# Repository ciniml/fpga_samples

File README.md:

# FPGA Samples

GOWIN LittleBeeなどの小規模FPGA向けのサンプルやライブラリ

## 内容

### rtl

SystemVerilogで記述したモジュール

### src/main/scala

Chisel3で記述したモジュール

### src/test/scala

Chisel3で記述したモジュールのテスト

## ライセンス

Boost Software License 1.0

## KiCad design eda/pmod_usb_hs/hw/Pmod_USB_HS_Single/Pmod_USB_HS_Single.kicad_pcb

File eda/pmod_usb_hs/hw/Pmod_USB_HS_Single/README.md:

# Pmod USB HS Single (Rev. A)

USB 2.0 HS デバイスを Pmod 1 個でつなぐ基板。Gowin USB 2.0 SoftPHY の Single LVDS 配線から
D- 側の比較器を省き、FPGA ピン 7 本 + VBUS 検出 1 本に収めた。KiCad 10。

- FPGA 側: `rtl/usb/gowin/usb_phy_gowin_sl.v` の `CMP1=1`
- 設計検討: [`../../SINGLE_PMOD.md`](../../SINGLE_PMOD.md)
- PHY の動作確認: SLogic16U3 で HS を実機確認済み (`eda/slogic16u3_usb2`、`make HS=1 CMP1=1`)

状態: **設計のみ (未発注・実機未確認)**。ERC / DRC (回路図との一致を含む) はエラー 0。

## 仕様

- 外形 22.86 × 27.94 mm、2 層 1.6 mm (FR4)、角 1.27 mm 面取り。
- J1: Pmod 2x6 直角ヘッダ (TangFPGAExtensions の `Conn_Pmod_Spec_B_Thin`)、基板下端。
- J2: USB Type-C レセプタクル、HRO TYPE-C-31-M-12 (USB 2.0 の 16 ピン)、基板上端。デバイス (UFP) 専用。
- D+/D- の結合ペア:
  - 寸法は Pmod_RPiCamera と同じ 0.1661 / 0.127 mm (USB ネットクラス)。
  - F.Cu のみで引き、B.Cu は全面 GND。
  - B.Cu を通るのは、コネクタのピン列の D-/D+ 入れ替え 1 か所 (約 2 mm) だけ。ほかに VREF (直流) がヘッダの列の間で B.Cu を通る。
- ESD 保護: D1/D2 は TPD1E05U06DPY (0.42 pF、1 ライン 1 個)。
- VBUS は電源に使わず、検出だけに使う。R12/R13 で 5 V を 3.0 V に分圧する (LVCMOS33 の VIH 2.0 V を超える)。

## 回路 (TN710 USB2.0-RC、Arora-V の値)

| Ref | 値 | 役割 |
|---|---|---|
| R6, R7 | 100 Ω | dx 対の直列抵抗 (TN710 R6/R7)。送信と差動受信がこの対を共用する |
| R2, R3 | 33 Ω | HS 終端 (ピンの Low 駆動 + 33 Ω、TN710 R2/R3 は 36 Ω。JLC の Basic 部品にするため 33 Ω に変更、終端は約 42 Ω の見込み) |
| R1 | 1.5 kΩ | D+ プルアップ。PULLUP が High でアタッチ |
| R8 / R9 | 4.7 kΩ / 200 Ω | VREF = 3.3 V × 200 / 4900 ≈ 135 mV (D+ 比較器の N 側。TN710 は 1.8 kΩ / 75 Ω で 132 mV、Basic 部品にするため変更) |
| C1 | 1 µF | VREF のバイパス |
| R10, R11 | 5.1 kΩ | CC1/CC2 の Rd (UFP) |
| R12 / R13 | 100 kΩ / 150 kΩ | VBUS 検出の分圧 |
| C5 | 1 µF | VBUS |
| C3, C4 | 10 µF, 100 nF | 3.3 V のデカップリング |

- TN710 の R4/R5 (Dual LVDS の差動受信用 0 Ω) は Single 配線にはないので欠番にしてある。
- TN710 の定数表に合わせるため、部品番号はそのまま使っている (R2/R3 と R8/R9 の値は上記のとおり変更)。

## ピン割り当て

| Pmod | 信号 | FPGA の IO | Tang Primer 25K (pmod2) |
|---|---|---|---|
| 1 / 7 | DX_P / DX_N | LVCMOS33D 双方向 (ELVDS_IOBUF) | G11 / G10 |
| 2 / 8 | D+ / VREF | LVDS25 入力 (D+ 比較器) | D11 / D10 |
| 3 / 9 | TERM_DP / TERM_DN | LVCMOS33 双方向 (Low で終端、Hi-Z で FS 受信) | B11 / B10 |
| 4 | PULLUP | LVCMOS33 出力 | C11 |
| 10 | VBUS_DET | LVCMOS33 入力 (PULL_MODE=DOWN) | C10 |
| 5, 11 / 6, 12 | GND / 3.3 V | | |

制約の例と PHY のつなぎ方は `../../SINGLE_PMOD.md` の §3 と §4 にある。

## 配線の要点

- **コネクタのピン列**: 1 列の SMD パッドで D+/D- が交互に並ぶ (B6 D+、A7 D-、A6 D+、B7 D-)。
  - B6 と A6 はピン列の上 (コネクタ本体の下) でつないだ。
  - B7 は B.Cu に潜って D+ の下をくぐり、A7 側の D- に合流する。
  - VBUS の 2 パッドも同様に、ピン列の上でつないだ。
- **ペアからヘッダまで**: ESD のあと、D+/D- はペアのまま斜めに下りてヘッダ直上の TN710 網に入る。
  - D+ はバス状に分岐する: R6、比較器 → Pmod 2 (直進)、R2 → Pmod 3、R1 → Pmod 4。
  - D- は左へ分かれて R7 と R3 に入る。
- **dx 対 (R6/R7 → Pmod 1/7)**: HS の送受信を担うペア。
  - R6/R7 を横に並べ、出口からすぐ結合ペアにしてヘッダの左を下ろす。
  - ヘッダの 2 列の間に横から入り、そこで対称に分かれる (P は上の Pmod 1、N は下の Pmod 7)。
  - Pmod の差動ペアは上下の列で向かい合うので、上から入ると N だけが 2.54 mm 長くなる。横から入ってこれを避けた。
- **D- の終端 (R3 → Pmod 9)**: 基板の左端を下り、ヘッダ外側の列の下を通って Pmod 9 に下から入る。
- **VREF と VBUS_DET**:
  - VREF は Pmod 8 から B.Cu でヘッダの列の間を右へ抜け、ビアで表に戻る。直流で、真上 (F.Cu) に高速の信号はない。
  - VBUS_DET は Pmod 4 と 5 の間からヘッダの列の間 (F.Cu) に入り、Pmod 10 に届く。
- **配線長** (`gen_pcb.py` の基板から計測):
  - DX_P (R6 → Pmod 1) は 6.2 mm、DX_N (R7 → Pmod 7) は 6.7 mm。P/N の差は約 0.5 mm (約 3 ps)。
  - D- の終端経路 (R3 → Pmod 9) は 15.8 mm、D+ 側 (R2 → Pmod 3) は 2.5 mm。

## 製造データ

`tools/build.sh` が ERC / DRC (回路図との一致を含む) を通してから `fab/` を作る。

| ファイル | 内容 |
|---|---|
| `fab/Pmod_USB_HS_Single_gerber.zip` | ガーバー (F/B Cu、Mask、Silk、F.Paste、Edge) とドリル (PTH/NPTH 別) |
| `fab/Pmod_USB_HS_Single_bom.csv` | 部品表 (LCSC 番号、MPN 付き) |
| `fab/Pmod_USB_HS_Single_pos.csv` | 実装位置 (表面のみ) |
| `fab/jlc/Pmod_USB_HS_Single_jlc_bom.csv`, `_jlc_cpl.csv` | JLC 実装用の BOM / CPL (`tools/jlc_files.py`、LCSC 番号のない J1 は除く) |
| `fab/Pmod_USB_HS_Single_schematic.pdf` | 回路図 |
| `fab/*.png` | 3D レンダリング |
| `fab/erc.rpt`, `fab/drc.rpt` | 検査結果 (ライブラリ表の警告はヘッドレス環境に由来) |
| `fab/lcsc/Pmod_USB_HS_Single_lcsc_5pcs.csv` | LCSC 部品購入用 (5 枚分、J1 含む、2026-10-29 時点で約 $5.84)。`tools/lcsc_order.py N` で N 枚分を作り直す (LCSC に問い合わせて最小発注数・単価・在庫を反映、要ネットワーク、`build.sh` には含まない) |

回路図 (`tools/gen_sch.py`) と基板 (`tools/gen_pcb.py`、配置・配線・ベタを座標で記述) は最初スクリプトから生成した。
その後、基板は KiCad で手を入れている (F.Cu の +3V3 ベタ、配線の調整) ので、GUI 側を正とする。
`build.sh` は既定では再生成しない。`REGEN=1 tools/build.sh` で再生成すると GUI での修正は消える。
部品の LCSC 番号と MPN は `tools/gen_sch.py` の `PARTS` が正。変えたら `tools/gen_sch.py` → `tools/update_fields.py`
(配線を残したまま基板側の部品の欄だけ更新) → `tools/build.sh`。
裏面シルク (ロゴ、基板名 / 版 / 日付 / 作者、ピン表) は `tools/silk.py` が持つ。単体で実行すると、基板の裏面シルクだけをその場で入れ直す (銅箔は触らない)。
表面のリファレンス文字は circuitpnr (`cpnr labels`) で置き、`cpnr label-check` で重なり・パッド干渉・取り違えがないことを確かめた
(`gen_pcb.py` は非表示で作るので、`REGEN=1` のあとは置き直しが要る)。

## 部品

LCSC 番号は 2026-10-29 時点。JLC の Basic 部品があるものはそれを選んだ (JLC と LCSC の在庫は別)。JLC の拡張部品 (手数料あり) は D1/D2 と J2 の 2 種類、R13 は Preferred Extended。

| Ref | 部品 | LCSC | 備考 |
|---|---|---|---|
| J1 | 2x6 2.54 mm 直角ピンヘッダ | (C41417354) | 手はんだ。回路図には LCSC 番号なし。購入一覧では左の候補を使う (ピン長・本体寸法をフットプリントと要照合) |
| J2 | HRO TYPE-C-31-M-12 | C165948 | 16 ピン (USB 2.0)。外形 7.3 mm、前端は基板端から約 0.65 mm 出る (要実物確認) |
| D1, D2 | TI TPD1E05U06DPYR | C436349 | X1SON-2 (0.6 × 1.0 mm)。手はんだは難しい。同名の互換品 (TECH PUBLIC C907835、Leiditech C2972479) はクランプ電圧などが違うので使わない |
| R1 | 1.5 kΩ 1% 0402 UNI-ROYAL 0402WGF1501TCE | C25867 | |
| R2, R3 | 33 Ω 1% 0402 UNI-ROYAL 0402WGF330JTCE | C25105 | JLC Basic。LCSC 在庫切れのときは購入一覧で YAGEO RC0402FR-0733RL (C138002) に置き換わる |
| R6, R7 | 100 Ω 1% 0402 UNI-ROYAL 0402WGF1000TCE | C25076 | |
| R8 / R9 | 4.7 kΩ / 200 Ω 1% 0402 UNI-ROYAL | C25900 / C25087 | JLC Basic |
| R10, R11 | 5.1 kΩ 1% 0402 UNI-ROYAL 0402WGF5101TCE | C25905 | |
| R12 / R13 | 100 kΩ / 150 kΩ 1% 0402 UNI-ROYAL | C25741 / C25755 | |
| C1, C5 | 1 µF X5R 0402 Samsung CL05A105KA5NQNC | C52923 | LCSC で在庫切れのときは、購入一覧で YAGEO CC0402KRX5R7BB105 (C325464、16 V) などに置き換わる |
| C3 | 10 µF 10 V X5R 0603 Samsung CL10A106KP8NNNC | C19702 | |
| C4 | 100 nF X7R 0402 Samsung CL05B104KB54PNC | C307331 | LCSC 在庫切れのときは、購入一覧で Samsung CL05B104KO5NNNC (C1525、16 V) に置き換わる |

## 未確定事項

- **差動インピーダンス**: Pmod_RPiCamera と同じ寸法 (100 Ω 想定、2 層 1.6 mm でのペア結合が主体) で、USB の 90 Ω に合わせた計算はしていない。
  - 基板上の D+/D- は約 15 mm で、FPGA ボード側の Pmod 配線とヘッダの方が支配的。
  - 製造業者のスタックアップで要再計算。
- **定数**: R2/R3 と R8/R9 以外は TN710 の Arora-V の値そのままで、HS の振幅 (400 mV) と終端 (33 Ω + IO の ON 抵抗) は未実測。SLogic16U3 の実装値も不明。
  - R6/R7 (直列) と IO の DRIVE で振幅が決まる。
- **Pmod 経由の HS 品質**: 送受信が同じ dx 対を通るので、ヘッダから FPGA までの未整合区間が両方向に効く。`SINGLE_PMOD.md` §7 を参照。
- **Tang Primer 25K の pmod2**: G11/G10 を ELVDS_IOBUF (エミュレート差動の出力) にできるか、960 MHz の FCLK が届くかは合成で未確認。
- **J2**: 基板端に対する前後位置。

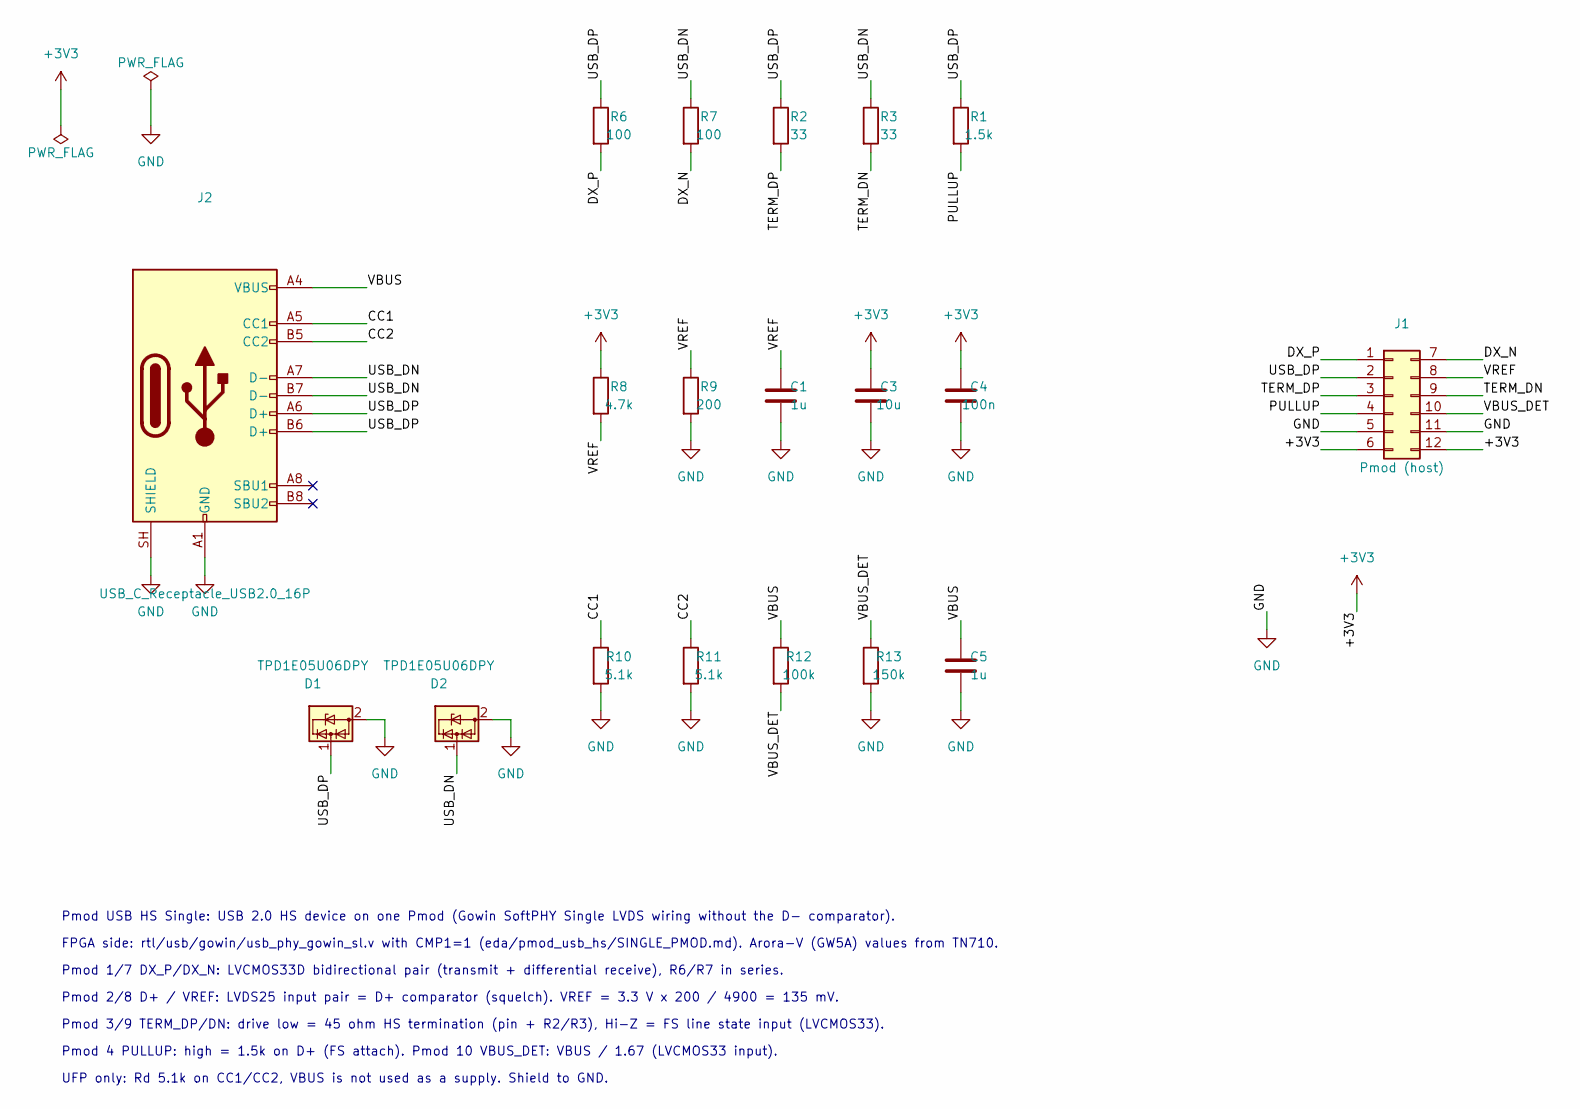
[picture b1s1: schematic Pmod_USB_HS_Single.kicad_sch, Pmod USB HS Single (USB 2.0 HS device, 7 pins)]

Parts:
C1, C5: 1u; C_0402_1005Metric; MPN Samsung CL05A105KA5NQNC; LCSC C52923
C3: 10u; C_0603_1608Metric; MPN Samsung CL10A106KP8NNNC; LCSC C19702
C4: 100n; C_0402_1005Metric; MPN Samsung CL05B104KB54PNC; LCSC C307331
D1, D2: TPD1E05U06DPY; Texas_DPY0002A_0.6x1mm_P0.65mm; MPN TI TPD1E05U06DPYR; LCSC C436349
J1: Pmod (host); Conn_Pmod_Spec_B_Thin
J2: USB_C_Receptacle_USB2.0_16P; USB_C_Receptacle_HRO_TYPE-C-31-M-12; MPN HRO TYPE-C-31-M-12; LCSC C165948
R1: 1.5k; R_0402_1005Metric; MPN UNI-ROYAL 0402WGF1501TCE; LCSC C25867
R2, R3: 33; R_0402_1005Metric; MPN UNI-ROYAL 0402WGF330JTCE; LCSC C25105
R6, R7: 100; R_0402_1005Metric; MPN UNI-ROYAL 0402WGF1000TCE; LCSC C25076
R8: 4.7k; R_0402_1005Metric; MPN UNI-ROYAL 0402WGF4701TCE; LCSC C25900
R9: 200; R_0402_1005Metric; MPN UNI-ROYAL 0402WGF2000TCE; LCSC C25087
R10, R11: 5.1k; R_0402_1005Metric; MPN UNI-ROYAL 0402WGF5101TCE; LCSC C25905
R12: 100k; R_0402_1005Metric; MPN UNI-ROYAL 0402WGF1003TCE; LCSC C25741
R13: 150k; R_0402_1005Metric; MPN UNI-ROYAL 0402WGF1503TCE; LCSC C25755

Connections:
+3V3: C3.1, C4.1, J1.6, J1.12, R8.1
/CC1: J2.A5 (CC1), R10.1
/CC2: J2.B5 (CC2), R11.1
/DX_N: J1.7, R7.2
/DX_P: J1.1, R6.2
/PULLUP: J1.4, R1.2
/TERM_DN: J1.9, R3.2
/TERM_DP: J1.3, R2.2
/USB_DN: D2.1 (I/O), J2.A7 (D-), J2.B7 (D-), R3.1, R7.1
/USB_DP: D1.1 (I/O), J1.2, J2.A6 (D+), J2.B6 (D+), R1.1, R2.1, R6.1
/VBUS: C5.1, J2.A4 (VBUS), J2.A9 (VBUS), J2.B4 (VBUS), J2.B9 (VBUS), R12.1
/VBUS_DET: J1.10, R12.2, R13.1
/VREF: C1.1, J1.8, R8.2, R9.1
GND: C1.2, C3.2, C4.2, C5.2, D1.2 (GND), D2.2 (GND), J1.5, J1.11, J2.A1 (GND), J2.A12 (GND), J2.B1 (GND), J2.B12 (GND), J2.SH (SHIELD), R9.2, R10.2, R11.2, R13.2

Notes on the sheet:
Pmod USB HS Single: USB 2.0 HS device on one Pmod (Gowin SoftPHY Single LVDS wiring without the D- comparator).
FPGA side: rtl/usb/gowin/usb_phy_gowin_sl.v with CMP1=1 (eda/pmod_usb_hs/SINGLE_PMOD.md). Arora-V (GW5A) values from TN710.
Pmod 1/7 DX_P/DX_N: LVCMOS33D bidirectional pair (transmit + differential receive), R6/R7 in series.
Pmod 2/8 D+ / VREF: LVDS25 input pair = D+ comparator (squelch). VREF = 3.3 V x 200 / 4900 = 135 mV.
Pmod 3/9 TERM_DP/DN: drive low = 45 ohm HS termination (pin + R2/R3), Hi-Z = FS line state input (LVCMOS33).
Pmod 4 PULLUP: high = 1.5k on D+ (FS attach). Pmod 10 VBUS_DET: VBUS / 1.67 (LVCMOS33 input).
UFP only: Rd 5.1k on CC1/CC2, VBUS is not used as a supply. Shield to GND.

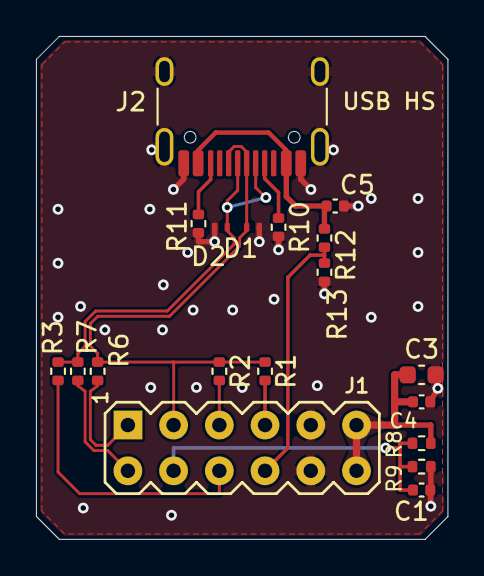
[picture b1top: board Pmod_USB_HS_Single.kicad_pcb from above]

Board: 2 copper layers, 22.9 x 27.9 mm, 20 parts (1 on the bottom side), 14 nets.

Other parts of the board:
LOGO1: Logo_Open_Hardware_Small; logo

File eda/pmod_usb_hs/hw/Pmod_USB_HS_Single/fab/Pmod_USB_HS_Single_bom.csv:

"Reference","Value","Footprint","QUANTITY","LCSC","MPN","Description"
"C1,C5","1u","Capacitor_SMD:C_0402_1005Metric","2","C52923","Samsung CL05A105KA5NQNC","1 uF 10 V X5R 0402 (VBUS),1 uF 10 V X5R 0402 (VREF)"
"C3","10u","Capacitor_SMD:C_0603_1608Metric","1","C19702","Samsung CL10A106KP8NNNC","10 uF 10 V X5R 0603"
"C4","100n","Capacitor_SMD:C_0402_1005Metric","1","C307331","Samsung CL05B104KB54PNC","100 nF 16 V X7R 0402"
"D1,D2","TPD1E05U06DPY","Package_SON:Texas_DPY0002A_0.6x1mm_P0.65mm","2","C436349","TI TPD1E05U06DPYR","1-channel ESD protection, 0.42 pF, X1SON-2"
"J1","Pmod (host)","local:Conn_Pmod_Spec_B_Thin","1","","","Pmod 2x6 right angle (Digilent Pmod Type 1A / spec B)"
"J2","USB_C_Receptacle_USB2.0_16P","Connector_USB:USB_C_Receptacle_HRO_TYPE-C-31-M-12","1","C165948","HRO TYPE-C-31-M-12","USB Type-C receptacle, USB 2.0 (16 pin)"
"R1","1.5k","Resistor_SMD:R_0402_1005Metric","1","C25867","UNI-ROYAL 0402WGF1501TCE","1.5k 1% 0402 (D+ pull-up, soft connect)"
"R2,R3","33","Resistor_SMD:R_0402_1005Metric","2","C25105","UNI-ROYAL 0402WGF330JTCE","33R 1% 0402 (HS termination, D+),33R 1% 0402 (HS termination, D-)"
"R6,R7","100","Resistor_SMD:R_0402_1005Metric","2","C25076","UNI-ROYAL 0402WGF1000TCE","100R 1% 0402 (dx series, D+),100R 1% 0402 (dx series, D-)"
"R8","4.7k","Resistor_SMD:R_0402_1005Metric","1","C25900","UNI-ROYAL 0402WGF4701TCE","4.7k 1% 0402 (VREF ~135 mV)"
"R9","200","Resistor_SMD:R_0402_1005Metric","1","C25087","UNI-ROYAL 0402WGF2000TCE","200R 1% 0402 (VREF)"
"R10,R11","5.1k","Resistor_SMD:R_0402_1005Metric","2","C25905","UNI-ROYAL 0402WGF5101TCE","5.1k 1% 0402 (CC1 Rd),5.1k 1% 0402 (CC2 Rd)"
"R12","100k","Resistor_SMD:R_0402_1005Metric","1","C25741","UNI-ROYAL 0402WGF1003TCE","100k 1% 0402 (VBUS divider, 5 V -> 3.0 V)"
"R13","150k","Resistor_SMD:R_0402_1005Metric","1","C25755","UNI-ROYAL 0402WGF1503TCE","150k 1% 0402 (VBUS divider)"

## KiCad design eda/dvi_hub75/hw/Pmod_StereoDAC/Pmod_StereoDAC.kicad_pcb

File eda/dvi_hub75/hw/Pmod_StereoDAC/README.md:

# Pmod Stereo DAC (Rev. A)

`eda/dvi_hub75` (`rtl/hdmi_rx`) の 1 bit ΔΣ DAC 出力 2 本 (L / R) を、RC ローパスと直流カットを通して
3.5 mm ステレオジャック (と 3 ピンヘッダ) に出す Pmod 基板。ライン出力。KiCad 10。

状態: **設計のみ (未発注・実機未確認)**。ERC / DRC (回路図との一致、ベタ再充填込み) はエラー 0。

## 回路 (チャネルごと、`eda/dvi_hub75/README.md` の LPF そのまま)

```
Pmod 1 (L) / 2 (R) ─ R1 1kΩ ─┬─ R2 10kΩ ─┬─ C3 1µF ─┬─→ ジャック (L = チップ / R = リング) と J3 (1 = L / 3 = R)
                             C1 3.3nF     C2 330pF   R3 100kΩ
                             │            │          │
                            GND          GND        GND
```

| 部品 | L | R | 値 |
|---|---|---|---|
| 1 段目 R / C | R1 / C1 | R11 / C11 | 1 kΩ / 3.3 nF C0G (約 48 kHz) |
| 2 段目 R / C | R2 / C2 | R12 / C12 | 10 kΩ / 330 pF C0G (約 48 kHz) |
| 直流カット | C3 | C13 | 1 µF X7R 50 V (0805) |
| ブリーダ | R3 | R13 | 100 kΩ (出力側の直流を 0 V に固定、抜き差しのポップ防止) |

- 周波数特性 (ピンの出力インピーダンス 30 Ω 込み、dvi_hub75 の計算): −3 dB 28.5 kHz、20 kHz で −1.6 dB、
  1 MHz で −53 dB、ΔΣ の更新周波数 6.19 MHz で −85 dB
- 20 kHz まで平坦にしたいなら C1 / C11 = 2.2 nF、C2 / C12 = 220 pF (−3 dB 約 43 kHz、20 kHz で −0.7 dB、
  6.19 MHz で約 −77 dB)。基板はそのまま、部品の値だけ変える
- 低域: C3 と R3 / 負荷 (47 kΩ 以上を想定) で −3 dB は 2〜4 Hz
- **ライン出力** (フルスケール正弦波で約 1.1 Vrms、出力インピーダンス約 10 kΩ)。**ヘッドホンは直接鳴らせない**
  (アンプ付きスピーカー、オーディオインターフェースのライン入力、ヘッドホンアンプにつなぐ)
- 音質は FPGA の I/O 電源のノイズで決まる (ΔΣ の出力は I/O 電源の電圧そのもの)。改善策は dvi_hub75 の README
  (静かな電源のフリップフロップで打ち直す) を参照。本基板は受動部品のみで 3.3 V は使わない

## コネクタ

| Pmod | 信号 | 備考 |
|---|---|---|
| 1 | AUDIO_L (ΔΣ 左) | |
| 2 | AUDIO_R (ΔΣ 右) | |
| 5, 11 | GND | |
| 3, 4, 7–10, 6 / 12 (3.3 V) | 未接続 | |

- J2: 3.5 mm ステレオジャック SHOU HAN **PJ-313D** (SMD、LCSC C668608)。チップ = L、リング = R、スリーブ = GND。
  プラグ挿入口は基板上端 (本体前面が基板端、ノーズ 2.5 mm がはみ出す)。各接点は 2 本足 (両側) で、
  フットプリントでは同じ番号のパッドを内部接続扱い (duplicate pad numbers are jumpers) にしてある
- J3: 1×3 2.54 mm ピンヘッダ (縦、LCSC C49257)、**1 = L、2 = GND、3 = R** (シルク L / G / R、ピン 1 は角パッド)。
  ジャックと並列 (直流カットの後、ブリーダ付き)。GND が中央なので、逆向きに挿しても L と R が短絡しない
- J1: Pmod 2×6 直角ヘッダ (TangFPGAExtensions の `Conn_Pmod_Spec_B_Thin`)、基板下端、ピン 1 左

FPGA 側の定義は `mod/pmod_stereo_dac/pmod_pins.csv` (dac_l = pmodN_1、dac_r = pmodN_2)。

### eda/dvi_hub75 で使う場合

dvi_hub75 は ΔΣ を J4 (40 ピンヘッダ) の 19 / 20 番 = D1 / E3 から出している。Tang Primer 25K の Pmod 3 スロットは
すべて使用中 (pmod0 = Pmod DVI、pmod1 / pmod2 = HUB75 ベースボード) なので、この基板は **J4 から Pmod を
取り出すアダプタ** (`eda/targets/tangprimer25k/hw` で別途設計中の J4 → Pmod 変換基板) に挿す。
`eda/dvi_hub75/src/tangprimer25k/pins.cst` の `dac_l` / `dac_r` の IO_LOC を、そのアダプタで本基板の
ピン 1 / 2 が来る FPGA ピンに変える (dvi_hub75 の設計自体はまだ変えていない)。
J4 19 / 20 番がアダプタの Pmod ピン 1 / 2 に来る配置なら pins.cst の変更は不要。

## 基板

- 外形 20.32 × 33.6 mm (Pmod 1 スロット幅)、2 層 1.6 mm、角 1.27 mm 面取り
- 2 チャネルを左右の列に配置 (L は Pmod ピン 1 の真上、R は鏡像)。直列部品は列上、信号は下から上 (ジャック側) へ。
  シャント部品 (C1 / C2 / R3) は列の内側に置き、それぞれ専用の GND ビアで裏面の全面 GND へ落とす
- 部品は 0603 (C3 / C13 のみ 0805)、手はんだも可
- 裏面: ロゴ、「Pmod / Stereo DAC / Rev.A / 2026-10-20」「Kenta Ida (@ciniml)」、Pmod ピンの凡例

## 部品 (LCSC / JLCPCB、2026-10-20 時点)

| Ref | 部品 | LCSC | 備考 |
|---|---|---|---|
| R1, R11 | UNI-ROYAL 0603WAF1001T5E (1 kΩ) | C21190 | JLC Basic。LCSC 在庫 0 → 購入リストは YAGEO RC0603FR-071KL (C22548) |
| R2, R12 | UNI-ROYAL 0603WAF1002T5E (10 kΩ) | C25804 | JLC Basic |
| R3, R13 | UNI-ROYAL 0603WAF1003T5E (100 kΩ) | C25803 | JLC Basic |
| C1, C11 | YAGEO CC0603JRNPO9BN332 (3.3 nF C0G) | C107048 | |
| C2, C12 | Samsung CL10C331JB8NNNC (330 pF C0G) | C1664 | JLC Basic |
| C3, C13 | Samsung CL21B105KBFNNNE (1 µF X7R 50 V 0805) | C28323 | JLC Basic。LCSC 在庫 0 → 購入リストは YAGEO CC0805KKX7R9BB105 (C91185) |
| J2 | SHOU HAN PJ-313D | C668608 | |
| J3 | BOOMELE 2.54-1*3P | C49257 | 手はんだ可 |
| J1 | 2×6 2.54 mm 直角ピンヘッダ | — | 手はんだ想定 (購入リストには候補 C41417354、寸法はフットプリントと要照合) |

## 製造データ (`tools/build.sh`)

| ファイル | 内容 |
|---|---|
| `fab/Pmod_StereoDAC_gerber.zip` | ガーバー + ドリル (PTH / NPTH 別) |
| `fab/Pmod_StereoDAC_bom.csv`, `_pos.csv` | 部品表 (LCSC / MPN 付き)、実装位置 (原点は基板左下) |
| `fab/jlc/` | JLCPCB 実装用 BOM / CPL (LCSC 番号のある部品。J3 は THT) |
| `fab/lcsc/Pmod_StereoDAC_lcsc_5pcs.csv` | LCSC 購入リスト 5 枚分 (`tools/lcsc_order.py N`、LCSC 在庫切れは同等品に自動置換) |
| `fab/Pmod_StereoDAC_schematic.pdf`, `*.png` | 回路図、レンダリング |

回路図・基板は `tools/gen_sch.py` / `tools/gen_pcb.py` で生成 (`./tools/build.sh --regen`)。KiCad で手を入れたら
以後は KiCad のファイルが正 (`--regen` は手修正を消す)。

## 未確認・注意

- PJ-313D のフットプリントは SHOU HAN の図面 (2020-08-24) から自作。KiCad 標準ライブラリに該当品が無いため。
  3D モデルは無い (レンダリングにジャックは写らない)。A / B / C 端子 = スリーブ / リング / チップは、
  挿入口に近い順 (A) とデータシートの接続図 (A が本体側) からの判断
- 実機のアナログ特性 (ノイズ、歪み) は未測定 (dvi_hub75 でも LPF 出力は未確認)

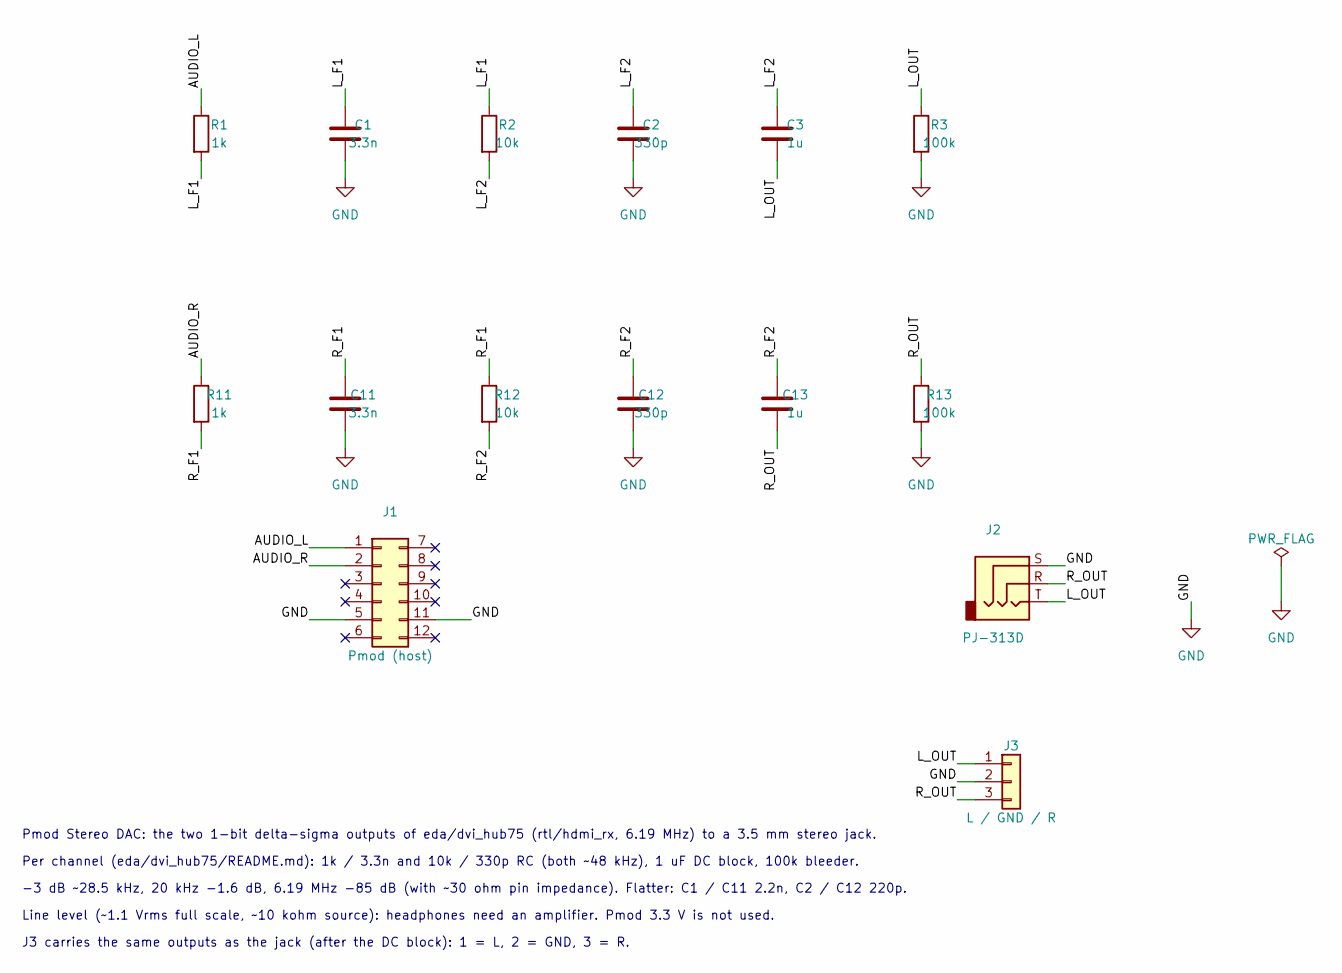
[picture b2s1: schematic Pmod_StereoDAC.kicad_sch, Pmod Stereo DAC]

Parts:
C1, C11: 3.3n; C_0603_1608Metric; MPN YAGEO CC0603JRNPO9BN332; LCSC C107048
C2, C12: 330p; C_0603_1608Metric; MPN Samsung CL10C331JB8NNNC; LCSC C1664
C3, C13: 1u; C_0805_2012Metric; MPN Samsung CL21B105KBFNNNE; LCSC C28323
J1: Pmod (host); Conn_Pmod_Spec_B_Thin; MPN 2x6 2.54 mm right-angle pin header (han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
J2: PJ-313D; Jack_3.5mm_SHOUHAN_PJ-313D_Horizontal; MPN SHOU HAN PJ-313D; LCSC C668608
J3: L / GND / R; PinHeader_1x03_P2.54mm_Vertical; MPN BOOMELE 2.54-1*3P; LCSC C49257
R1, R11: 1k; R_0603_1608Metric; MPN UNI-ROYAL 0603WAF1001T5E; LCSC C21190
R2, R12: 10k; R_0603_1608Metric; MPN UNI-ROYAL 0603WAF1002T5E; LCSC C25804
R3, R13: 100k; R_0603_1608Metric; MPN UNI-ROYAL 0603WAF1003T5E; LCSC C25803

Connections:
/AUDIO_L: J1.1, R1.1
/AUDIO_R: J1.2, R11.1
/L_F1: C1.1, R1.2, R2.1
/L_F2: C2.1, C3.1, R2.2
/L_OUT: C3.2, J2.T, J3.1, R3.1
/R_F1: C11.1, R11.2, R12.1
/R_F2: C12.1, C13.1, R12.2
/R_OUT: C13.2, J2.R, J3.3, R13.1
GND: C1.2, C2.2, C11.2, C12.2, J1.5, J1.11, J2.S, J3.2, R3.2, R13.2

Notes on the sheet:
Pmod Stereo DAC: the two 1-bit delta-sigma outputs of eda/dvi_hub75 (rtl/hdmi_rx, 6.19 MHz) to a 3.5 mm stereo jack.
Per channel (eda/dvi_hub75/README.md): 1k / 3.3n and 10k / 330p RC (both ~48 kHz), 1 uF DC block, 100k bleeder.
-3 dB ~28.5 kHz, 20 kHz -1.6 dB, 6.19 MHz -85 dB (with ~30 ohm pin impedance). Flatter: C1 / C11 2.2n, C2 / C12 220p.
Line level (~1.1 Vrms full scale, ~10 kohm source): headphones need an amplifier. Pmod 3.3 V is not used.
J3 carries the same outputs as the jack (after the DC block): 1 = L, 2 = GND, 3 = R.

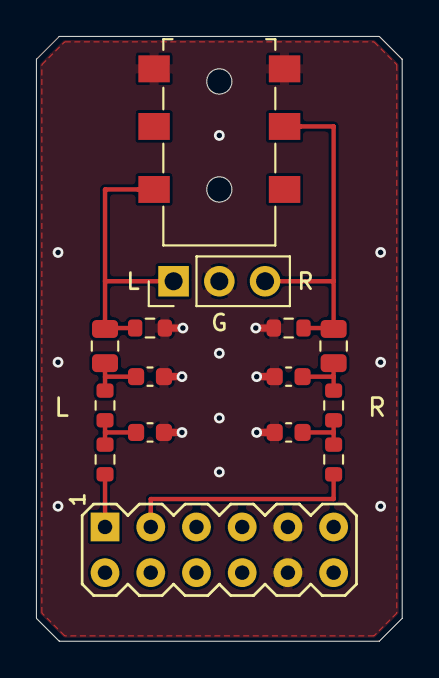
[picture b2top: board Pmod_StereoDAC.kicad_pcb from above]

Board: 2 copper layers, 20.3 x 33.6 mm, 16 parts (1 on the bottom side), 9 nets.

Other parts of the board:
LOGO1: logo

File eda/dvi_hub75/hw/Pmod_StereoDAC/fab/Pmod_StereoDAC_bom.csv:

"Reference","Value","Footprint","QUANTITY","LCSC","MPN","Description"
"C1,C11","3.3n","Capacitor_SMD:C_0603_1608Metric","2","C107048","YAGEO CC0603JRNPO9BN332","3.3 nF 50 V C0G 5% 0603"
"C2,C12","330p","Capacitor_SMD:C_0603_1608Metric","2","C1664","Samsung CL10C331JB8NNNC","330 pF 50 V C0G 5% 0603"
"C3,C13","1u","Capacitor_SMD:C_0805_2012Metric","2","C28323","Samsung CL21B105KBFNNNE","1 uF 50 V X7R 10% 0805 (DC block)"
"J1","Pmod (host)","local:Conn_Pmod_Spec_B_Thin","1","","2x6 2.54 mm right-angle pin header (hand soldered)","Pmod 2x6 right angle (Digilent Pmod Type 1A / spec B)"
"J2","PJ-313D","local:Jack_3.5mm_SHOUHAN_PJ-313D_Horizontal","1","C668608","SHOU HAN PJ-313D","3.5 mm stereo jack, SMD (SHOU HAN PJ-313D): tip = L, ring = R, sleeve = GND"
"J3","L / GND / R","Connector_PinHeader_2.54mm:PinHeader_1x03_P2.54mm_Vertical","1","C49257","BOOMELE 2.54-1*3P","1x03 2.54 mm pin header, vertical: 1 = L, 2 = GND, 3 = R (line out, after the DC block)"
"R1,R11","1k","Resistor_SMD:R_0603_1608Metric","2","C21190","UNI-ROYAL 0603WAF1001T5E","1 kOhm 1% 0603"
"R2,R12","10k","Resistor_SMD:R_0603_1608Metric","2","C25804","UNI-ROYAL 0603WAF1002T5E","10 kOhm 1% 0603"
"R3,R13","100k","Resistor_SMD:R_0603_1608Metric","2","C25803","UNI-ROYAL 0603WAF1003T5E","100 kOhm 1% 0603"

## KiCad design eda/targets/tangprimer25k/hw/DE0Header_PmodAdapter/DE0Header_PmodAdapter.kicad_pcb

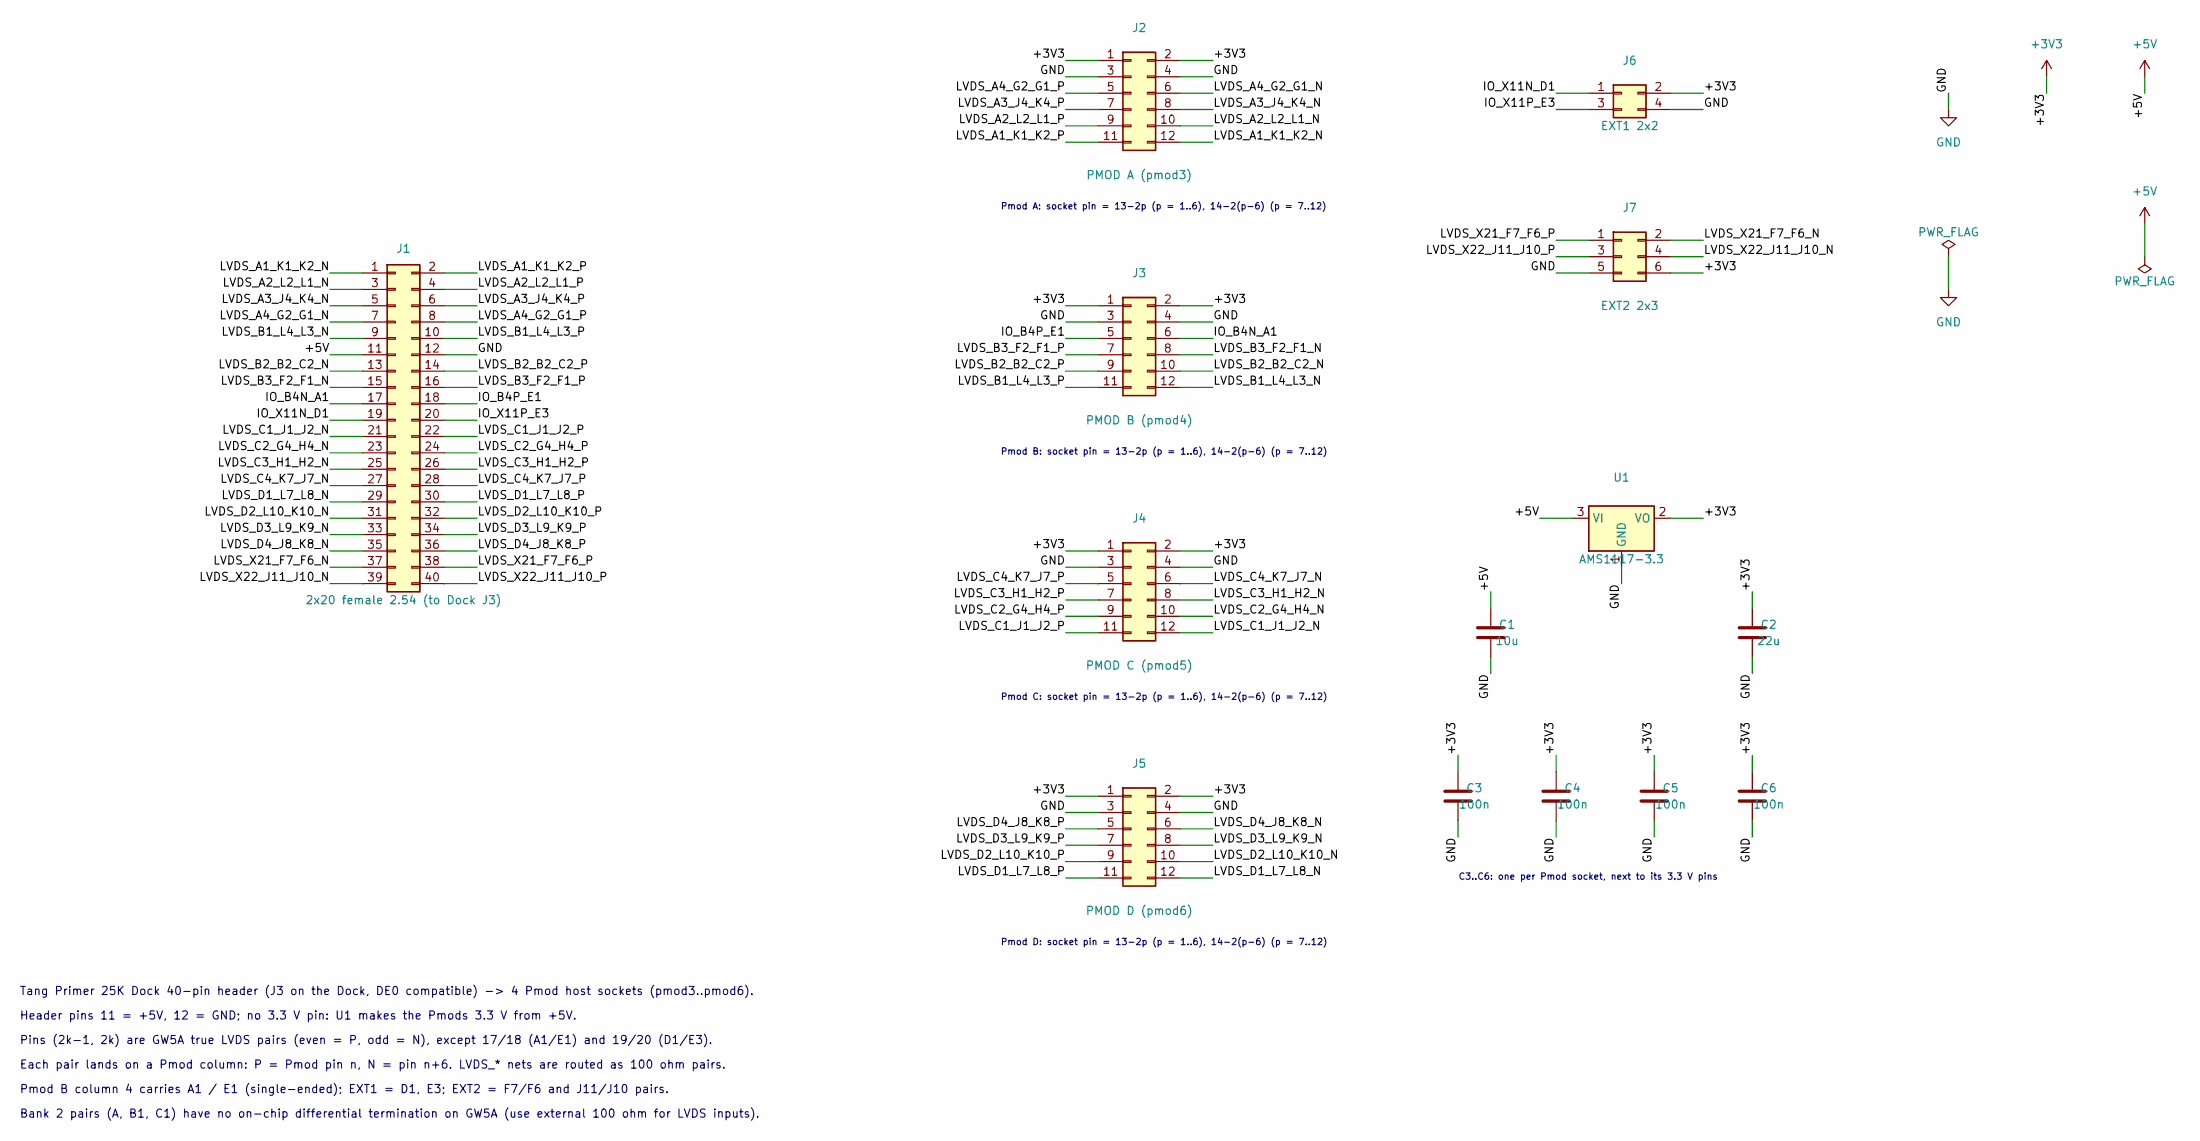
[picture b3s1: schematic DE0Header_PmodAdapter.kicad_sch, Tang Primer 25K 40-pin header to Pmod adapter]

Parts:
C1: 10u; C_0805_2012Metric; MPN Samsung CL21A106KAYNNNE; LCSC C15850
C2: 22u; C_0805_2012Metric; MPN Samsung CL21A226MAQNNNE; LCSC C45783
C3, C4, C5, C6: 100n; C_0402_1005Metric; MPN Samsung CL05B104KO5NNNC; LCSC C1525
J1: 2x20 female 2.54 (to Dock J3); PinSocket_2x20_P2.54mm_Vertical; MPN BOOMELE 2.54-2*20P; LCSC C5124634
J2: PMOD A (pmod3); PinSocket_2x06_P2.54mm_Horizontal; MPN Hong Cheng HC-PM254-8.5H-2x6PW; LCSC C22373932
J3: PMOD B (pmod4); PinSocket_2x06_P2.54mm_Horizontal; MPN Hong Cheng HC-PM254-8.5H-2x6PW; LCSC C22373932
J4: PMOD C (pmod5); PinSocket_2x06_P2.54mm_Horizontal; MPN Hong Cheng HC-PM254-8.5H-2x6PW; LCSC C22373932
J5: PMOD D (pmod6); PinSocket_2x06_P2.54mm_Horizontal; MPN Hong Cheng HC-PM254-8.5H-2x6PW; LCSC C22373932
J6: EXT1 2x2; PinHeader_2x02_P2.54mm_Vertical; MPN BOOMELE 2.54-2*2PPin; LCSC C66690
J7: EXT2 2x3; PinHeader_2x03_P2.54mm_Vertical; MPN BOOMELE 2.54-2*3PPin; LCSC C65114
U1: AMS1117-3.3; SOT-223-3_TabPin2; MPN AMS AMS1117-3.3; LCSC C6186

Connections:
+3V3: C2.1, C3.1, C4.1, C5.1, C6.1, J2.1, J2.2, J3.1, J3.2, J4.1, J4.2, J5.1, J5.2, J6.2, J7.6, U1.2 (VO)
+5V: C1.1, J1.11, U1.3 (VI)
/IO_B4N_A1: J1.17, J3.6
/IO_B4P_E1: J1.18, J3.5
/IO_X11N_D1: J1.19, J6.1
/IO_X11P_E3: J1.20, J6.3
/LVDS_A1_K1_K2_N: J1.1, J2.12
/LVDS_A1_K1_K2_P: J1.2, J2.11
/LVDS_A2_L2_L1_N: J1.3, J2.10
/LVDS_A2_L2_L1_P: J1.4, J2.9
/LVDS_A3_J4_K4_N: J1.5, J2.8
/LVDS_A3_J4_K4_P: J1.6, J2.7
/LVDS_A4_G2_G1_N: J1.7, J2.6
/LVDS_A4_G2_G1_P: J1.8, J2.5
/LVDS_B1_L4_L3_N: J1.9, J3.12
/LVDS_B1_L4_L3_P: J1.10, J3.11
/LVDS_B2_B2_C2_N: J1.13, J3.10
/LVDS_B2_B2_C2_P: J1.14, J3.9
/LVDS_B3_F2_F1_N: J1.15, J3.8
/LVDS_B3_F2_F1_P: J1.16, J3.7
/LVDS_C1_J1_J2_N: J1.21, J4.12
/LVDS_C1_J1_J2_P: J1.22, J4.11
/LVDS_C2_G4_H4_N: J1.23, J4.10
/LVDS_C2_G4_H4_P: J1.24, J4.9
/LVDS_C3_H1_H2_N: J1.25, J4.8
/LVDS_C3_H1_H2_P: J1.26, J4.7
/LVDS_C4_K7_J7_N: J1.27, J4.6
/LVDS_C4_K7_J7_P: J1.28, J4.5
/LVDS_D1_L7_L8_N: J1.29, J5.12
/LVDS_D1_L7_L8_P: J1.30, J5.11
/LVDS_D2_L10_K10_N: J1.31, J5.10
/LVDS_D2_L10_K10_P: J1.32, J5.9
/LVDS_D3_L9_K9_N: J1.33, J5.8
/LVDS_D3_L9_K9_P: J1.34, J5.7
/LVDS_D4_J8_K8_N: J1.35, J5.6
/LVDS_D4_J8_K8_P: J1.36, J5.5
/LVDS_X21_F7_F6_N: J1.37, J7.2
/LVDS_X21_F7_F6_P: J1.38, J7.1
/LVDS_X22_J11_J10_N: J1.39, J7.4
/LVDS_X22_J11_J10_P: J1.40, J7.3
GND: C1.2, C2.2, C3.2, C4.2, C5.2, C6.2, J1.12, J2.3, J2.4, J3.3, J3.4, J4.3, J4.4, J5.3, J5.4, J6.4, J7.5, U1.1 (GND)

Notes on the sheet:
Pmod A: socket pin = 13-2p (p = 1..6), 14-2(p-6) (p = 7..12)
Pmod B: socket pin = 13-2p (p = 1..6), 14-2(p-6) (p = 7..12)
Pmod C: socket pin = 13-2p (p = 1..6), 14-2(p-6) (p = 7..12)
Pmod D: socket pin = 13-2p (p = 1..6), 14-2(p-6) (p = 7..12)
C3..C6: one per Pmod socket, next to its 3.3 V pins
Tang Primer 25K Dock 40-pin header (J3 on the Dock, DE0 compatible) -> 4 Pmod host sockets (pmod3..pmod6).
Header pins 11 = +5V, 12 = GND; no 3.3 V pin: U1 makes the Pmods 3.3 V from +5V.
Pins (2k-1, 2k) are GW5A true LVDS pairs (even = P, odd = N), except 17/18 (A1/E1) and 19/20 (D1/E3).
Each pair lands on a Pmod column: P = Pmod pin n, N = pin n+6. LVDS_* nets are routed as 100 ohm pairs.
Pmod B column 4 carries A1 / E1 (single-ended); EXT1 = D1, E3; EXT2 = F7/F6 and J11/J10 pairs.
Bank 2 pairs (A, B1, C1) have no on-chip differential termination on GW5A (use external 100 ohm for LVDS inputs).

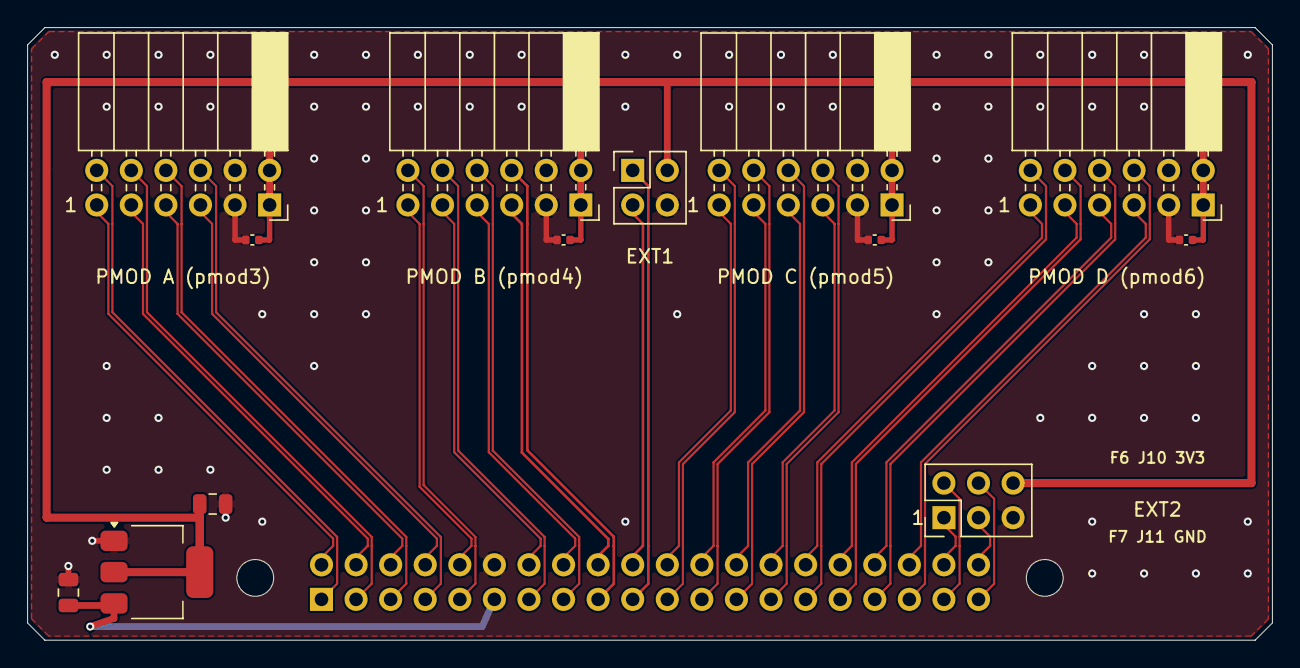
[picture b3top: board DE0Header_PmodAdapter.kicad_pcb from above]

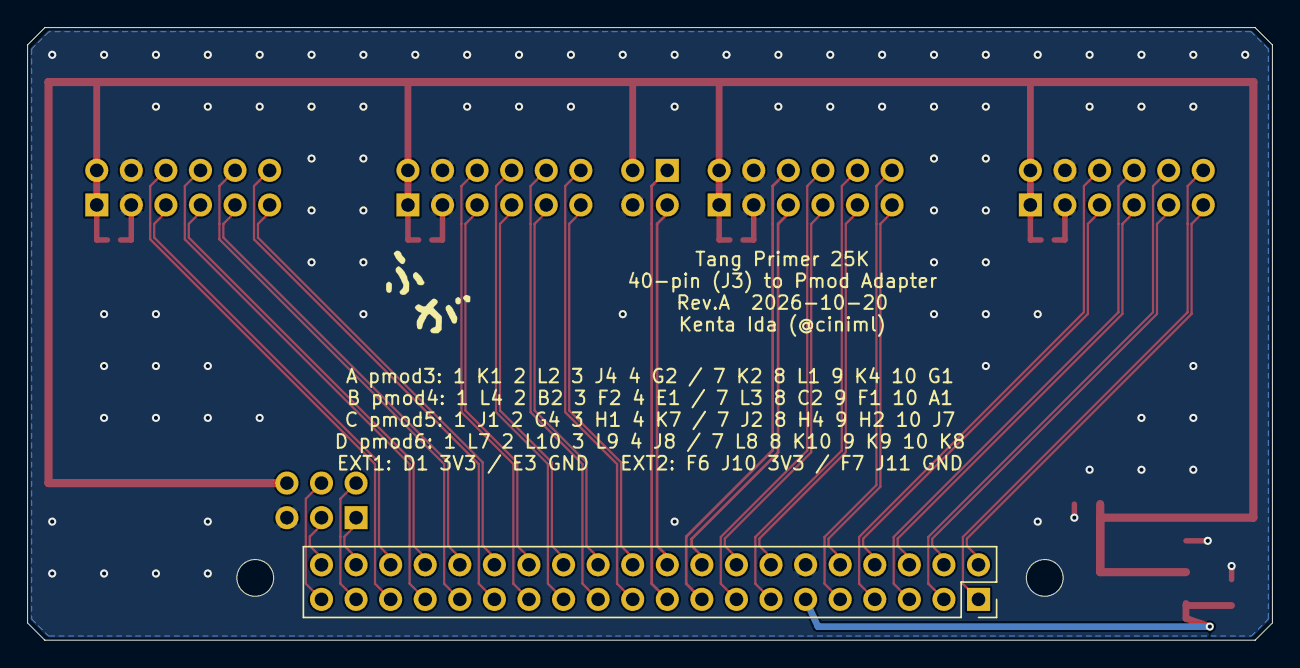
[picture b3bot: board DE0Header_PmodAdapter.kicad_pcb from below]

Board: 2 copper layers, 91.4 x 45.0 mm, 17 parts (2 on the bottom side), 41 nets.

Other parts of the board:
H1, H2: MountingHole_2.7mm_M2.5_ISO7380
LOGO1: logo

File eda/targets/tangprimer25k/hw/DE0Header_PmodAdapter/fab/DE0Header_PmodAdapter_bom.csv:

"Reference","Value","Footprint","QUANTITY","LCSC","MPN","Description"
"C1","10u","Capacitor_SMD:C_0805_2012Metric","1","C15850","Samsung CL21A106KAYNNNE","10 uF 25 V X5R 0805 (LDO input)"
"C2","22u","Capacitor_SMD:C_0805_2012Metric","1","C45783","Samsung CL21A226MAQNNNE","22 uF 25 V X5R 0805 (LDO output)"
"C3,C4,C5,C6","100n","Capacitor_SMD:C_0402_1005Metric","4","C1525","Samsung CL05B104KO5NNNC","100 nF 16 V X7R 0402 (Pmod 3.3 V)"
"J1","2x20 female 2.54 (to Dock J3)","Connector_PinSocket_2.54mm:PinSocket_2x20_P2.54mm_Vertical","1","C5124634","BOOMELE 2.54-2*20P","2x20 2.54 mm female socket, 8.5 mm, mounted on the bottom side"
"J2","PMOD A (pmod3)","Connector_PinSocket_2.54mm:PinSocket_2x06_P2.54mm_Horizontal","1","C22373932","Hong Cheng HC-PM254-8.5H-2x6PW","Pmod host: 2x6 2.54 mm right-angle female socket"
"J3","PMOD B (pmod4)","Connector_PinSocket_2.54mm:PinSocket_2x06_P2.54mm_Horizontal","1","C22373932","Hong Cheng HC-PM254-8.5H-2x6PW","Pmod host: 2x6 2.54 mm right-angle female socket"
"J4","PMOD C (pmod5)","Connector_PinSocket_2.54mm:PinSocket_2x06_P2.54mm_Horizontal","1","C22373932","Hong Cheng HC-PM254-8.5H-2x6PW","Pmod host: 2x6 2.54 mm right-angle female socket"
"J5","PMOD D (pmod6)","Connector_PinSocket_2.54mm:PinSocket_2x06_P2.54mm_Horizontal","1","C22373932","Hong Cheng HC-PM254-8.5H-2x6PW","Pmod host: 2x6 2.54 mm right-angle female socket"
"J6","EXT1 2x2","Connector_PinHeader_2.54mm:PinHeader_2x02_P2.54mm_Vertical","1","C66690","BOOMELE 2.54-2*2PPin","2x2 2.54 mm pin header"
"J7","EXT2 2x3","Connector_PinHeader_2.54mm:PinHeader_2x03_P2.54mm_Vertical","1","C65114","BOOMELE 2.54-2*3PPin","2x3 2.54 mm pin header"
"U1","AMS1117-3.3","Package_TO_SOT_SMD:SOT-223-3_TabPin2","1","C6186","AMS AMS1117-3.3","3.3 V 1 A LDO (5 V from the header pin 11)"
